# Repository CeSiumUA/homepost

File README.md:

# Homepost

Homepost is an ESP32-based home monitoring and automation hub that combines BLE tracking, environmental sensing, radiation monitoring, and MQTT integration into a single device.

## Features

- **BLE iBeacon Tracking**: Detects and tracks iBeacon devices for presence detection (e.g., phone tracking)
- **HTU21 Temperature & Humidity Sensor**: Monitors environmental conditions via I2C and publishes data via MQTT
- **Geiger Counter Integration**: Monitors radiation levels and publishes data via MQTT
- **WiFi Connectivity**:
  - Station mode for connecting to existing networks
  - SoftAP mode for initial configuration
  - Automatic reconnection with configurable retry intervals
- **HTTP Server**: Web-based configuration interface
- **MQTT Publishing**: Sends sensor data and presence information to an MQTT broker
- **NVS Storage**: Persistent storage for WiFi credentials, MQTT settings, and configuration

## Hardware Requirements

- ESP32 development board (4MB flash minimum)
- HTU21D temperature/humidity sensor (I2C, default: SDA=GPIO21, SCL=GPIO22)
- Geiger counter sensor (connected via GPIO)
- Power supply (USB or external)

> **Note**: A custom PCB design is available in the `hardware/` directory (KiCad 8 format).

## Software Dependencies

- ESP-IDF v5.5 or later
- FreeRTOS (included with ESP-IDF)

## Building the Project

### Prerequisites

1. Install ESP-IDF following the [official installation guide](https://docs.espressif.com/projects/esp-idf/en/latest/esp32/get-started/index.html)
2. Set up the ESP-IDF environment:

   ```bash
   . $HOME/esp/esp-idf/export.sh
   ```

### Configure

Configure the project using menuconfig:

```bash
idf.py menuconfig
```

Navigate to `homepost configuration` to customize:

- **BT Options**: Bluetooth device name, inquiry length
- **Scanner Options**: RSSI filters, iBeacon major/minor IDs, scan timeout
- **WiFi Configuration**: SoftAP credentials, reconnection settings
- **HTTP Server Configuration**: Port settings
- **Storage Configuration**: NVS keys for credentials

### Build

Build the project:

```bash
idf.py build
```

### Flash

Flash the firmware to your ESP32:

```bash
idf.py -p PORT flash
```

Replace `PORT` with your ESP32's serial port (e.g., `COM3` on Windows or `/dev/ttyUSB0` on Linux).

### Monitor

View the serial output:

```bash
idf.py -p PORT monitor
```

Or combine flash and monitor:

```bash
idf.py -p PORT flash monitor
```

## Configuration

### Initial Setup

1. On first boot, the device will create a WiFi access point named `HOMEPOST` (default password: `12345678`)
2. Connect to this network and access the web interface at `http://192.168.4.1`
3. Configure:
   - WiFi credentials for your home network
   - MQTT broker settings (address, port, credentials)
   - MQTT topic base (runtime configurable via web interface)
   - iBeacon tracking parameters
   - Publish intervals

### iBeacon Tracking

Configure the iBeacon major and minor IDs to match the devices you want to track:

- `HOMEPOST_SCAN_MAJOR_FILTER`: Major ID (default: 100)
- `HOMEPOST_SCAN_MINOR_FILTER`: Minor ID (default: 40004)
- `HOMEPOST_SCAN_TIMEOUT_MINUTES`: How long to wait before marking device as absent (default: 2 minutes)

### MQTT Topics

The device publishes to topics under the configured base topic:

- `{topic}/homepost_version`: Firmware version in JSON format (`{"version": "X.Y.Z"}`), published on MQTT connection
- `{topic}/phone_present`: Presence detection status (iBeacon tracking)
- `{topic}/phone_rssi`: BLE RSSI signal strength in JSON format (`{"rssi": -XX}`) when device is present
- `{topic}/temperature`: Temperature readings in JSON format (`{"temperature": XX.XX}`)
- `{topic}/humidity`: Humidity readings in JSON format (`{"humidity": XX.XX}`)
- `{topic}/geiger`: Geiger counter CPM (counts per minute) data

### HTU21 Temperature & Humidity Sensor

Configure the HTU21 sensor via menuconfig:

- `HOMEPOST_HTU21_TIMER_PERIOD_MS`: Reading interval (default: 60000ms / 1 minute)
- `HOMEPOST_HTU21_I2C_SDA_GPIO`: I2C SDA pin (default: GPIO 21)
- `HOMEPOST_HTU21_I2C_SCL_GPIO`: I2C SCL pin (default: GPIO 22)
- `HOMEPOST_HTU21_I2C_FREQ_HZ`: I2C clock frequency (default: 100kHz)

## Project Structure

```text
homepost/
├── CMakeLists.txt              # Project configuration
├── sdkconfig                   # Build configuration
├── main/
│   ├── main.c                  # Application entry point
│   ├── wifi.c                  # WiFi connection management
│   ├── http_server.c           # Web configuration interface
│   ├── ble_scanner.c           # BLE scanning functionality
│   ├── ble_ibeacon.c           # iBeacon protocol handling
│   ├── tracker_scanner.c       # Presence tracking logic
│   ├── geiger_counter.c        # Radiation sensor integration
│   ├── htu21_sensor.c          # HTU21 temperature/humidity sensor
│   ├── mqtt_connection.c       # MQTT client
│   ├── internal_storage.c      # NVS storage management
│   ├── ota_update.c            # OTA firmware update
│   └── Kconfig.projbuild       # Configuration menu
├── inc/                        # Header files
└── hardware/                   # KiCad PCB design files
    └── manufacturing/          # Gerber files for PCB fabrication
```

## OTA (Over-The-Air) Updates

Homepost supports automatic firmware updates from GitHub releases.

### Requirements

1. **Flash Size**: Requires 4MB flash (configured in `menuconfig` → `Serial flasher config` → `Flash size`)

2. **Partition Table**: Must use OTA-compatible partition layout. In `menuconfig`:
   - Navigate to `Partition Table`
   - Select `Two large size OTA partitions` (required for 4MB flash with OTA)

3. **Bootloader Rollback** (recommended): Enable automatic rollback on failed boot:
   - Navigate to `Bootloader config`
   - Enable `CONFIG_BOOTLOADER_APP_ROLLBACK_ENABLE`

### GitHub Release Format

When creating releases on GitHub:

- **Tag format**: `release-v{version}` (e.g., `release-v1.3.0`)
- **Asset filename**: `homepost-{version}.bin` (e.g., `homepost-1.3.0.bin`)

### OTA Configuration

Configure OTA settings via `menuconfig` → `homepost configuration` → `OTA Update Configuration`:

- `HOMEPOST_OTA_ENABLED`: Enable/disable OTA updates (default: enabled)
- `HOMEPOST_OTA_GITHUB_OWNER`: GitHub repository owner/organization
- `HOMEPOST_OTA_GITHUB_REPO`: Repository name (default: `homepost`)
- `HOMEPOST_OTA_CHECK_INTERVAL_HOURS`: Update check interval (default: 4 hours)
- `HOMEPOST_OTA_INITIAL_DELAY_SECONDS`: Delay before first check (default: 30 seconds)

### Manual Update

Access the web interface and use the "Firmware Update" section to:

- View current and available versions
- Check for updates manually
- Trigger an update installation

### API Endpoints

- `GET /check-update`: Returns JSON with version info
- `POST /trigger-update`: Triggers immediate update check and installation

## Hardware Design

The `hardware/` directory contains a complete KiCad 8 project for a custom Homepost PCB:

- **Schematic**: `homepost.kicad_sch`
- **PCB Layout**: `homepost.kicad_pcb`
- **Manufacturing Files**: `manufacturing/` directory contains Gerber files and drill files ready for PCB fabrication

## Troubleshooting

### WiFi Connection Issues

- Check the serial monitor for connection status
- Verify credentials are correct via the web interface
- The device will retry connection every 3 minutes by default

### MQTT Connection Problems

- Verify broker address and port are correct
- Check firewall settings on the broker
- Ensure credentials (if required) are properly configured

### BLE Scanning Not Working

- Verify the iBeacon major/minor IDs match your tracking device
- Check RSSI threshold if filtering is enabled
- Ensure Bluetooth (BLE advertising) is enabled on the tracking device

### HTU21 Sensor Not Working

- Verify I2C wiring: SDA to GPIO21, SCL to GPIO22 (default pins)
- Check that the sensor is powered (3.3V)
- Review serial monitor for I2C initialization errors
- Ensure no I2C address conflicts (HTU21 uses address 0x40)

## License

This project is provided as-is for personal and educational use.

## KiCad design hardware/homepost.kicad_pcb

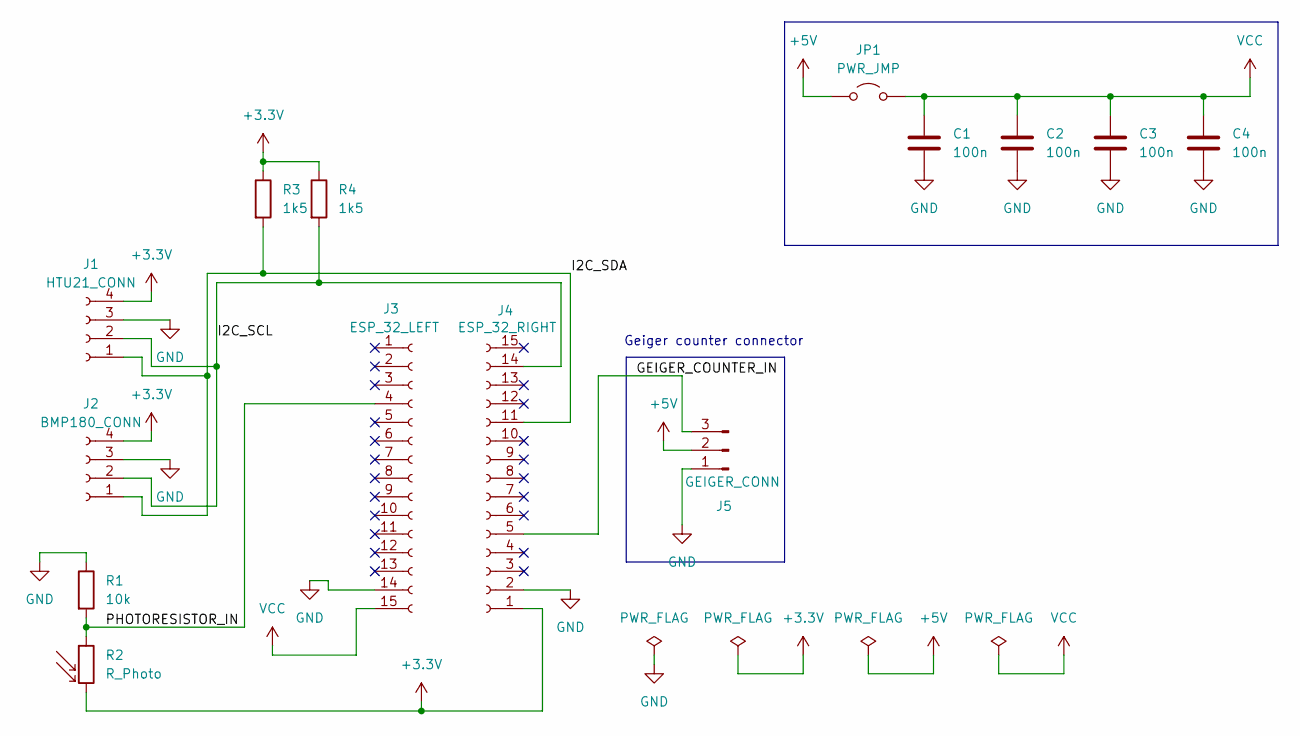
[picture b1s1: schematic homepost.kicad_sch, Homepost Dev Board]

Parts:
C1, C2, C3, C4: 100n; C_0402_1005Metric
J1: HTU21_CONN; PinSocket_1x04_P2.54mm_Vertical
J2: BMP180_CONN; PinSocket_1x04_P2.54mm_Vertical
J3: ESP_32_LEFT; PinSocket_1x15_P2.54mm_Vertical
J4: ESP_32_RIGHT; PinSocket_1x15_P2.54mm_Vertical
J5: GEIGER_CONN; PinHeader_1x03_P2.54mm_Vertical
JP1: PWR_JMP; PinHeader_1x02_P2.54mm_Vertical
R1: 10k; R_Axial_DIN0204_L3.6mm_D1.6mm_P5.08mm_Horizontal
R2: R_Photo; R_Axial_DIN0204_L3.6mm_D1.6mm_P5.08mm_Horizontal
R3, R4: 1k5; R_0402_1005Metric

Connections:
+3.3V: J1.4, J2.4, J4.1, R2.2, R3.1, R4.1
+5V: J5.2, JP1.1 (A)
/GEIGER_COUNTER_IN: J4.5, J5.3
/I2C_SCL: J1.2, J2.2, J4.14, R4.2
/I2C_SDA: J1.1, J2.1, J4.11, R3.2
/PHOTORESISTOR_IN: J3.4, R1.2, R2.1
GND: C1.2, C2.2, C3.2, C4.2, J1.3, J2.3, J3.14, J4.2, J5.1, R1.1
VCC: C1.1, C2.1, C3.1, C4.1, J3.15, JP1.2 (B)

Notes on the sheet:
Geiger counter connector

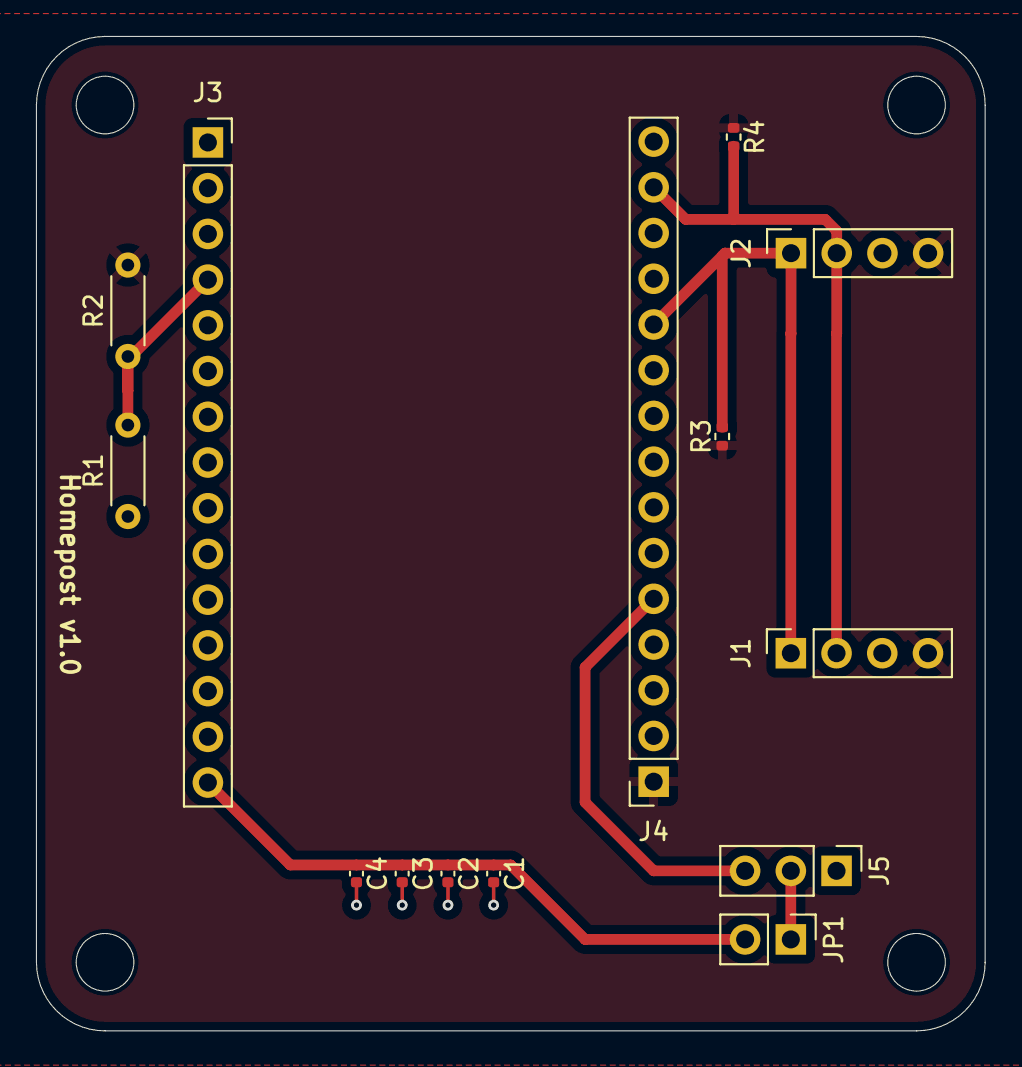
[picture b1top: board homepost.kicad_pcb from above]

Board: 2 copper layers, 52.7 x 55.2 mm, 14 parts (0 on the bottom side), 8 nets.

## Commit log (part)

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2025-03-02 Initialize sample project with basic structure and Docker support
2025-03-02 Add BLE scanner and internal storage components with initialization logic
2025-03-05 Add BLE scanner implementation and workspace configuration
2025-03-14 Refactor BLE scanner to tracker scanner and update related components
2025-03-14 Update scanner configuration and implement RSSI filtering in tracker scanner
2025-03-15 Enhance tracker scanner with RSSI filtering and task handle initialization
2025-03-15 Add WiFi credentials storage configuration and implement related functions
2025-03-15 Implement WiFi credentials management and HTTP server initialization
2025-03-16 Fix WiFi connection logic to start soft AP when credentials are not preserved
2025-03-16 Added WiFi with provisioning (http server) (#2)
    * Add WiFi credentials storage configuration and implement related functions
    * Implement WiFi credentials management and HTTP server initialization
    * Fix WiFi connection logic to start soft AP when credentials are not preserved
2025-03-16 Add GitHub Actions workflow for project build
2025-03-16 Remove push trigger from GitHub Actions workflow for pull requests only
2025-03-16 Remove push trigger and delete redundant workflow file for pull requests only
2025-03-16 Add esp-idf clean step to GitHub Actions workflow
2025-03-16 Add extra_docker_args to homepost_pr_build.yml for container naming
2025-03-16 Remove esp-idf clean step and add container removal in GitHub Actions workflow
2025-03-16 Refactor container name handling in GitHub Actions workflow
2025-03-16 Add step to remove build directory in GitHub Actions workflow
2025-03-16 Remove redundant step to delete build directory in GitHub Actions workflow
2025-03-16 Add GitHub Actions workflow for project build (#4)
    * Add GitHub Actions workflow for project build
    * Remove push trigger from GitHub Actions workflow for pull requests only
    * Remove push trigger and delete redundant workflow file for pull requests only
    * Add esp-idf clean step to GitHub Actions workflow
    * Add extra_docker_args to homepost_pr_build.yml for container naming
    * Remove esp-idf clean step and add container removal in GitHub Actions workflow
2025-03-18 Add MQTT configuration and storage support
2025-04-24 Refactor HTTP server URIs and update web forms for WiFi and MQTT configuration
2025-04-24 Add WiFi reconnection timer configuration and implement reconnection logic
2025-04-25 Implement MQTT connection handling and configuration options
2025-04-25 Add MQTT publish event handling and message publishing logic
2025-04-25 Implement MQTT configuration handling and add MQTT connection management functions
2025-04-25 Change TAG variable to static in main.c and mqtt_connection.c for better encapsulation
2025-08-19 Add MQTT client ID configuration to HTTP server and MQTT connection handling
2025-08-19 Update Docker args in CI workflow to ensure container removal
2025-08-19 5 add mqtt broker connection (#6)
    * Add MQTT configuration and storage support
    * Refactor HTTP server URIs and update web forms for WiFi and MQTT configuration
    * Add WiFi reconnection timer configuration and implement reconnection logic
    * Implement MQTT connection handling and configuration options
    * Add MQTT publish event handling and message publishing logic
    * Implement MQTT configuration handling and add MQTT connection management functions
2025-08-19 Add geiger_counter functionality and integrate with main application
2025-08-19 Add Geiger counter configuration and update MQTT publish queue function
2025-08-19 Update Geiger counter input pin definition and ISR handler; adjust timer period for improved performance
2025-08-19 Update Geiger counter configuration: disable pull-up resistor and extend timer period to 60 seconds
2025-08-19 Fix average CPM calculation to ensure proper floating-point division
2025-08-19 Add geiger_counter functionality and integrate with main application (#8)
    * Add geiger_counter functionality and integrate with main application
    * Add Geiger counter configuration and update MQTT publish queue function
    * Update Geiger counter input pin definition and ISR handler; adjust timer period for improved performance
    * Update Geiger counter configuration: disable pull-up resistor and extend timer period to 60 seconds
    * Fix average CPM calculation to ensure proper floating-point division
2025-08-20 Update radiation payload size and change MQTT topic to living_room/radiation
2025-08-20 Reduce MQTT and tracker scanner task stack sizes to optimize memory usage
2025-08-20 Update MQTT topic configuration and enhance tracker scanner functionality
2025-08-20 Add scan timeout configuration and update scanner timeout logic
2025-08-20 9 add mqtt message publishing for device presence (#10)
    * Update radiation payload size and change MQTT topic to living_room/radiation
    * Reduce MQTT and tracker scanner task stack sizes to optimize memory usage
    * Update MQTT topic configuration and enhance tracker scanner functionality
    * Add scan timeout configuration and update scanner timeout logic
2025-12-16 Implement feature X to enhance user experience and optimize performance
2025-12-16 Updated ESP-IDF version to v5.5.1
2025-12-16 Add comprehensive documentation for Homepost project
2025-12-16 Update ESP-IDF version to v5.5.1 in CI workflow
2025-12-16 Update README.md to enhance WiFi connectivity section and improve project setup instructions
2026-01-27 Fix MQTT connection handling on startup to improve reliability
2026-01-27 Fix MQTT connection handling on startup to improve reliability (#16)
2026-01-31 Add HTU21 sensor support with configuration options and MQTT integration
2026-01-31 Add cleanup step to GitHub Actions workflow and update cSpell dictionary
2026-01-31 Add logging for temperature and humidity readings in HTU21 sensor
2026-01-31 Refactor HTU21 sensor commands to use non-hold modes and adjust data buffer sizes
2026-01-31 Add HTU21 sensor support with configuration options and MQTT integration (#19)
    * Add HTU21 sensor support with configuration options and MQTT integration
    * Add cleanup step to GitHub Actions workflow and update cSpell dictionary
    * Add logging for temperature and humidity readings in HTU21 sensor
    * Refactor HTU21 sensor commands to use non-hold modes and adjust data buffer sizes
2026-02-01 Refactor cleanup step in CI workflow to use Docker for workspace management
2026-02-01 Add CI workflow for automatic release build and update sdkconfig for versioning
2026-02-01 Add release job to CI workflow for automatic firmware releases
2026-02-01 Added a Release build in GH actions (#21)
    * Refactor cleanup step in CI workflow to use Docker for workspace management
    * Add CI workflow for automatic release build and update sdkconfig for versioning
    * Add release job to CI workflow for automatic firmware releases
2026-02-01 Add documentation for version handling and update requirements
2026-02-01 Updated documentation (#23)
    * Add documentation for version handling and update requirements
    * Update README and documentation to include HTU21 sensor details and increment project version to 1.2.0
2026-02-02 Add plan for OTA update support via GitHub Releases
2026-02-02 Add OTA update support with GitHub integration and web interface
2026-02-03 Update partition configuration for OTA support and adjust flash size settings
2026-02-03 Update SDK configuration for versioning and initialization settings
2026-02-03 Update IDF initialization version to 5.5.1 in sdkconfig
2026-02-03 26 prepare partition config for ota (#27)
    * Update partition configuration for OTA support and adjust flash size settings
    * Update SDK configuration for versioning and initialization settings
    * Update IDF initialization version to 5.5.1 in sdkconfig
2026-02-03 Add BLE scanner stop and deinit functions; update OTA process to stop MQTT connection
2026-02-03 17 add ota update support (#24)
    * Add plan for OTA update support via GitHub Releases
    * Add OTA update support with GitHub integration and web interface
    * Add BLE scanner stop and deinit functions; update OTA process to stop MQTT connection
2026-02-04 Add manufacturing files for homepost project
    - Created homepost-job.gbrjob file containing board specifications, design rules, and material stackup.
    - Added homepost.drl file with drill specifications for various hole sizes and positions.
2026-02-04 Update SDK configuration for versioning and initialization
2026-02-04 REnamed configuration section to avoid duplication
2026-02-04 29 add hardware design files (#30)
    * Add manufacturing files for homepost project
    - Created homepost-job.gbrjob file containing board specifications, design rules, and material stackup.
    - Added homepost.drl file with drill specifications for various hole sizes and positions.
    * Update SDK configuration for versioning and initialization
    * Updated README.md
    * REnamed configuration section to avoid duplication
2026-02-04 add firmware version publishing on MQTT connection
2026-02-04 add firmware version publishing on MQTT connection (#31)
2026-02-05 make MQTT topic configurable at runtime via web interface and NVS storage
2026-02-05 hide update button by default and apply consistent styling
2026-02-05 add input validation for WiFi and MQTT connection forms
2026-02-05 Made MQTT topic configurable at runtime via web interface (#34)
    * make MQTT topic configurable at runtime via web interface and NVS storage
    * hide update button by default and apply consistent styling
    * add input validation for WiFi and MQTT connection forms
2026-02-05 Implement synchronous check for updates via GitHub releases API
2026-02-05 Implement synchronous check for updates via GitHub releases API (#37)
    * Implement synchronous check for updates via GitHub releases API
    * Update IDF initialization version and increment application project version to 1.4.4
2026-02-05 Remove automatic update check on page load
2026-02-05 Remove automatic update check on page load (#39)
2026-02-05 Revert "Remove automatic update check on page load (#39)"
    This reverts commit fe648b40de8ebc1b8dfaf0d525dd5a4952fa6721.
2026-02-05 Revert "Implement synchronous check for updates via GitHub releases API (#37)"
    This reverts commit 67efffa9936355a10b7dea973bd5d72c5c8110c7.
2026-02-05 Update version number to 1.4.6 and modify button display for firmware update
2026-02-05 40 fix version loading (#41)
    * Revert "Remove automatic update check on page load (#39)"
    This reverts commit fe648b40de8ebc1b8dfaf0d525dd5a4952fa6721.
    * Revert "Implement synchronous check for updates via GitHub releases API (#37)"
    This reverts commit 67efffa9936355a10b7dea973bd5d72c5c8110c7.
    * Update version number to 1.4.6 and modify button display for firmware update
2026-02-06 Add config endpoint to retrieve stored NVS values and update web UI
    - Implemented GET /config to return stored WiFi and MQTT settings as JSON, excluding passwords.
    - Updated web interface to pre-populate fields with stored values and display placeholders for passwords.
    - Enhanced form submission to skip saving unchanged passwords when using placeholder.
2026-02-06 Add config endpoint to retrieve stored NVS values and update web UI (#42)
    - Implemented GET /config to return stored WiFi and MQTT settings as JSON, excluding passwords.
    - Updated web interface to pre-populate fields with stored values and display placeholders for passwords.
    - Enhanced form submission to skip saving unchanged passwords when using placeholder.
2026-02-06 Add BLE RSSI publishing to MQTT topic for presence detection
2026-02-06 Add BLE RSSI publishing to MQTT topic for presence detection (#43)
